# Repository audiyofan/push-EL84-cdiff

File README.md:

# push-EL84-cdiff
Yves Monmagnon designed EL84 push pull with AOP différential feedback.

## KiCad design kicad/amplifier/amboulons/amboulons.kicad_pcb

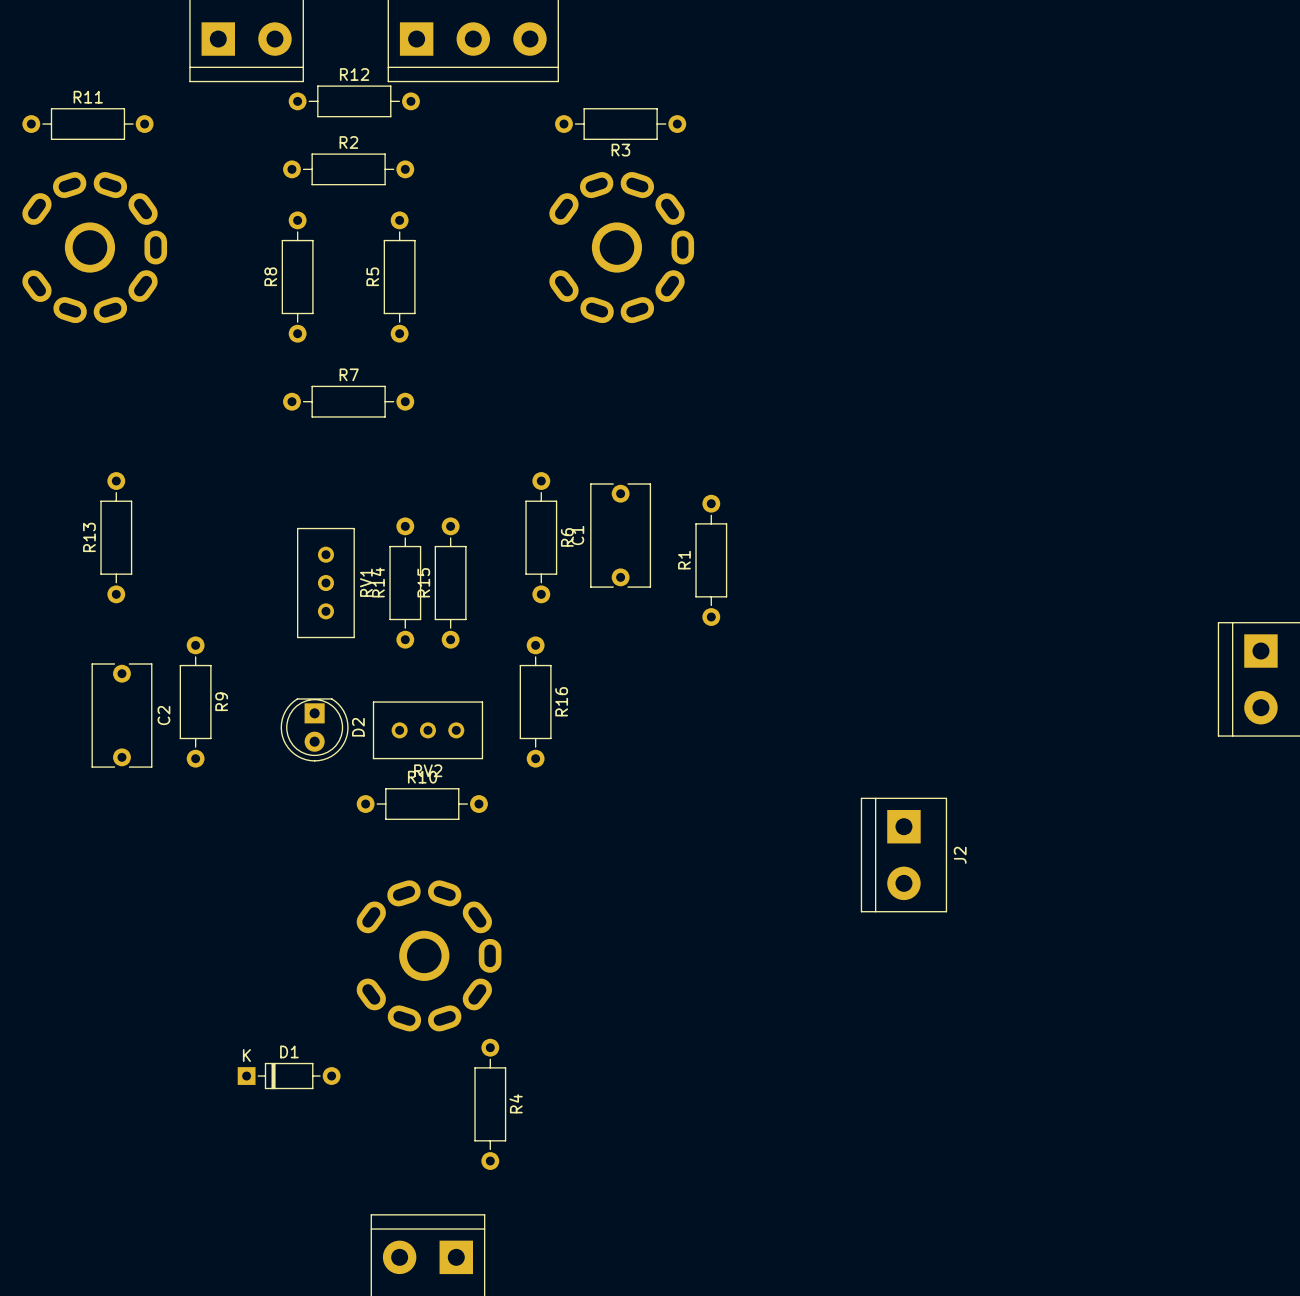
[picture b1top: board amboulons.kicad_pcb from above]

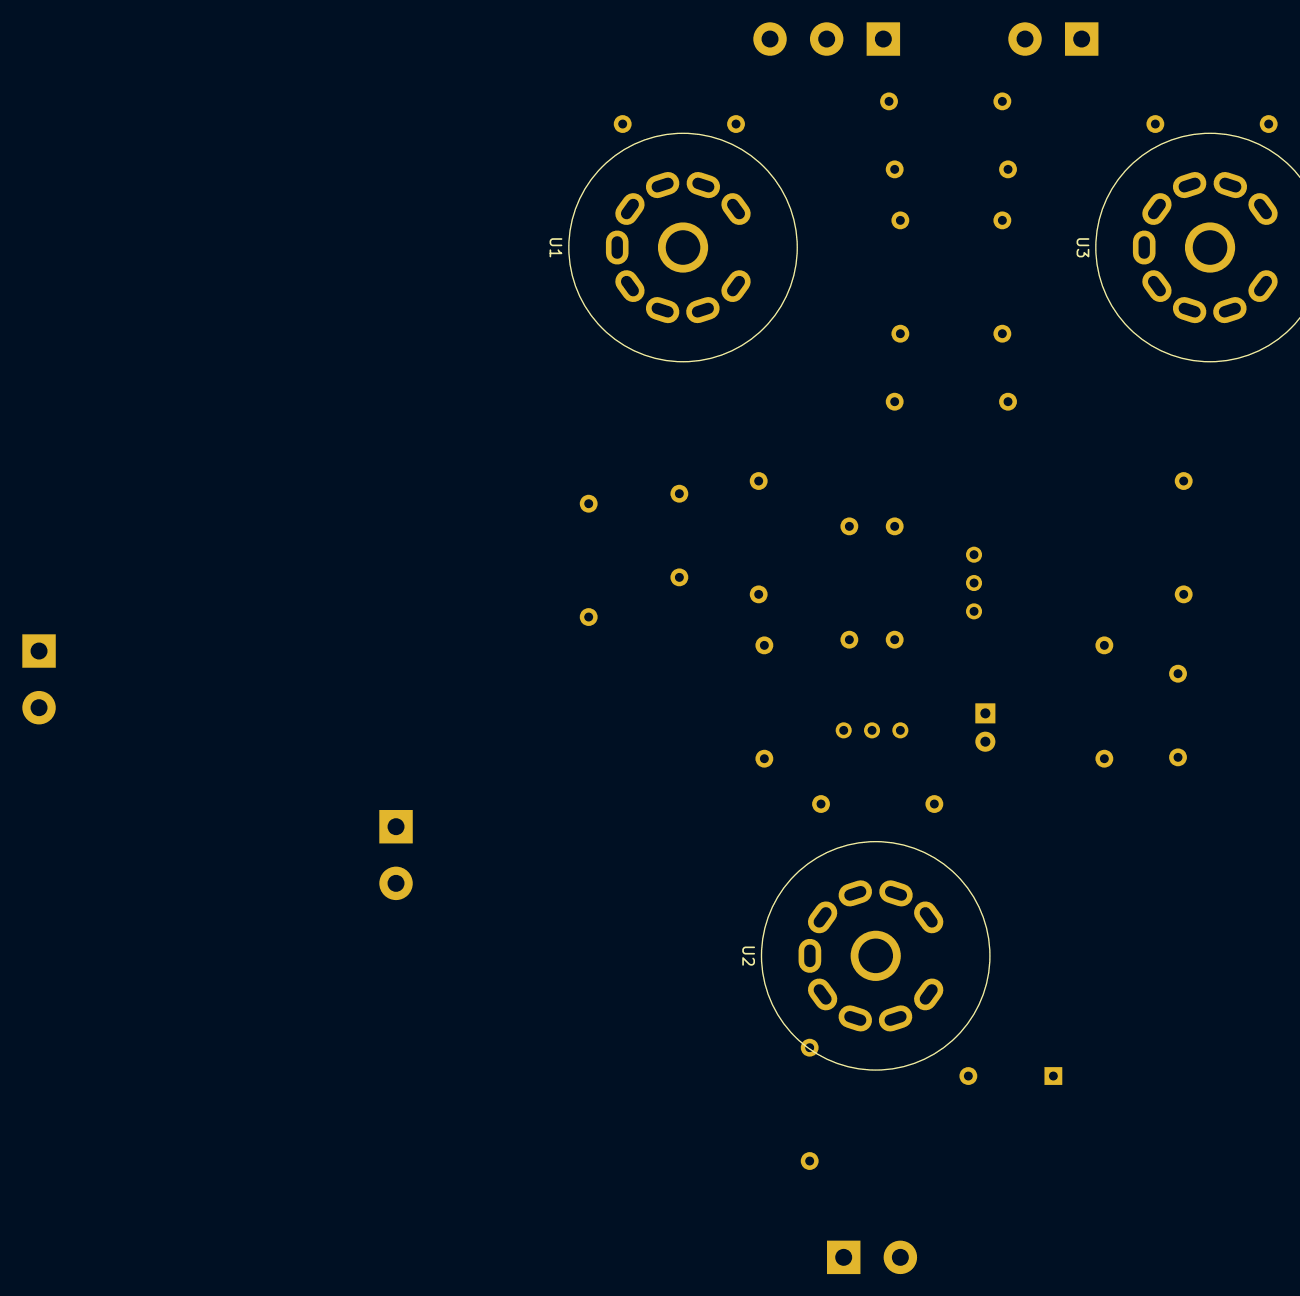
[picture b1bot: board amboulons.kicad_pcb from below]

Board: 2 copper layers, 30 parts (3 on the bottom side), 29 nets, no tracks yet.

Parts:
C1, C2: 47n; C_Rect_L9.0mm_W5.1mm_P7.50mm_MKT
D1: 1N5299; D_DO-35_SOD27_P7.62mm_Horizontal
D2: GREEN; LED_D5.0mm
J1, J2, J3, J5: Screw_Terminal_01x02; TerminalBlock_bornier-2_P5.08mm
J4: Screw_Terminal_01x03; TerminalBlock_bornier-3_P5.08mm
R1, R13: 470k; R_Axial_DIN0207_L6.3mm_D2.5mm_P10.16mm_Horizontal
R2, R12, R16: 100; R_Axial_DIN0207_L6.3mm_D2.5mm_P10.16mm_Horizontal
R3, R11: 10; R_Axial_DIN0207_L6.3mm_D2.5mm_P10.16mm_Horizontal
R4, R10: 1k; R_Axial_DIN0207_L6.3mm_D2.5mm_P10.16mm_Horizontal
R5, R8: 100k; R_Axial_DIN0207_L6.3mm_D2.5mm_P10.16mm_Horizontal
R6, R9: 220k; R_Axial_DIN0207_L6.3mm_D2.5mm_P10.16mm_Horizontal
R7: 12k; R_Axial_DIN0207_L6.3mm_D2.5mm_P10.16mm_Horizontal
R14, R15: 4.7k; R_Axial_DIN0207_L6.3mm_D2.5mm_P10.16mm_Horizontal
RV1: 4.7k; Potentiometer_Bourns_3296W_Vertical
RV2: 2.2k; Potentiometer_Bourns_3296W_Vertical
U1, U3: EL84; Valve_ECC-83-2
U2: ECC83; Valve_ECC-83-2

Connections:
/+250REG: J4.1, R2.1, R12.2
/-15V: D1.1, J4.2, R14.2, R15.2
/Anode-A: J3.1, R8.2, U3.7
/Anode-B: J3.2, R5.2, U1.7
/BIAS-A: R13.2, R14.1, RV2.1
/BIAS-B: R1.2, R15.1, RV2.3
/FB: J5.2, R10.1
/IN: J5.1, R4.2
GND: D2.2, J4.3, R3.2, R11.2, R16.1
unnamed: C1.1, R6.2, U2.6
unnamed: C1.2, R1.1, U1.2
unnamed: C2.1, R13.1, U3.2
unnamed: C2.2, R9.2, U2.1
unnamed: D1.2, U2.3, U2.8
unnamed: D2.1, RV1.1
unnamed: J1.1, U1.5, U3.5
unnamed: J1.2, U1.4, U3.4
unnamed: J2.1, U2.4
unnamed: J2.2, U2.5
unnamed: R2.2, U1.9
unnamed: R3.1, U1.3
unnamed: R4.1, U2.7
unnamed: R5.1, R6.1, R7.2
unnamed: R7.1, R8.1, R9.1
unnamed: R10.2, U2.2
unnamed: R11.1, U3.3
unnamed: R12.1, U3.9
unnamed: R16.2, U2.9
unnamed: RV1.2, RV1.3, RV2.2

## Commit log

2017-01-31 initial design
2017-02-12 update schema
2017-02-14 use Rauch structure for cdiff
2017-02-28 permuter le fusible & la CTN avec l'interrupteur

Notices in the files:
kicad/amplifier/amboulons/amboulons.kicad_pcb:
Licence CC-by-sa
